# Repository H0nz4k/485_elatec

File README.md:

# 485_elatec

Hardware concept for an ELATEC TWN4 MultiTech 3 BLE carrier board with RS-485 / OSDP, wide-range DC input, door lock outputs, and a Raspberry Pi-side RS-485 gateway.

## Current contents

- `analyza_twn4_carrier.md` - design analysis and architecture notes
- `schema_twn4_carrier_rev_a.md` - first schematic-level design proposal
- `rpi_gateway_hw.md` - Raspberry Pi RS-485 gateway / HAT notes
- `kicad/twn4_access_system/` - KiCad concept schematic for the reader carrier and RPi gateway

The design is currently Rev A concept-level work. It still needs component selection, footprint assignment, detailed ERC review, PCB layout, and bench validation before hardware production.

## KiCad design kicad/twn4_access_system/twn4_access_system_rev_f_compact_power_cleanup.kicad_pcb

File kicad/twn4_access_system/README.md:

# KiCad: TWN4 access system

This is a concept KiCad project for two related hardware blocks:

- reader-side TWN4 carrier / door module
- Raspberry Pi-side RS-485 gateway / HAT

The project contains two schematic sheets:

- `twn4_access_system.kicad_sch` - Rev A concept drawing
- `twn4_access_system_rev_b.kicad_sch` - Rev B schematic draft with concrete symbols, named nets, candidate footprints, and both reader-side and Raspberry Pi-side hardware

The Rev B electrical design notes and preliminary BOM are documented in:

- `../../schema_electrical_rev_b.md`
- `../../bom_rev_b.csv`

Current Rev B KiCad status:

- netlist export works and contains the real schematic components/nets
- Rev B now includes explicit service-prototype passives, RS-485 termination/bias options, lock/relay/input support parts and testpoints
- ERC has no error-severity findings after the current pass
- remaining ERC messages are warnings from embedded one-off symbols and intentionally single-ended configuration nets
- no Rev B PCB has been validated yet

Next KiCad step: replace the embedded placeholder-style symbols with proper library symbols/aliases, lock exact manufacturer footprints, then create the first service PCB layout.

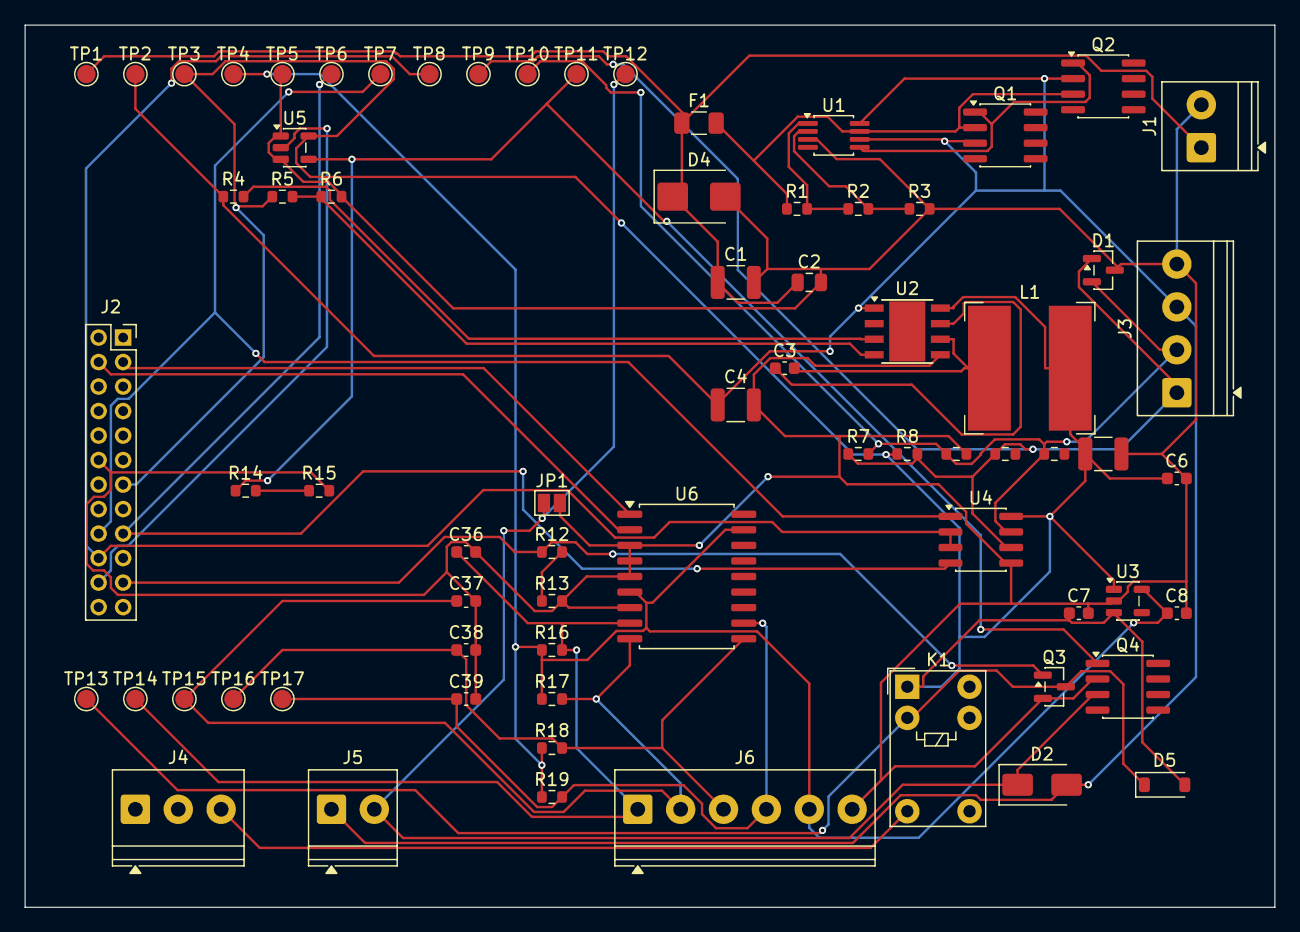
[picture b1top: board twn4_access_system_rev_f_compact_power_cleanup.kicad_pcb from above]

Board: 2 copper layers, 102.0 x 72.0 mm, 72 parts (0 on the bottom side), 32 nets.

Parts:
C1: 4.7uF 100V X7R input bulk; C_1210_3225Metric
C2: 100nF 100V input HF; C_0805_2012Metric
C3: 100nF BST; C_0603_1608Metric
C4: 22uF 100V buck input; C_1210_3225Metric
C5: 47uF 10V buck output; C_1210_3225Metric
C6: 100nF 5V HF; C_0603_1608Metric
C7: 1uF 3V3 LDO in; C_0603_1608Metric
C8: 1uF 3V3 LDO out; C_0603_1608Metric
C36: 10nF DOOR_IN filter; C_0603_1608Metric
C37: 10nF REX_IN filter; C_0603_1608Metric
C38: 10nF TAMPER_IN filter; C_0603_1608Metric
C39: 10nF AUX_IN filter; C_0603_1608Metric
D1: SM712 RS-485 TVS; SOT-23
D2: Lock flyback diode/TVS placeholder; D_SMA
D4: SMBJ58A input TVS; D_SMB
D5: Relay flyback diode; D_SOD-123
F1: 1.5A 60V+ fuse/PTC; Fuse_1206_3216Metric
J1: VIN 12-48V IN; TerminalBlock_Phoenix_PT-1,5-2-3.5-H_1x02_P3.50mm_Horizontal
J2: TWN4 MultiTech 3 BLE X2 socket; PinSocket_2x12_P2.00mm_Vertical
J3: RS-485 OUT A/B/+VIN/GND; TerminalBlock_Phoenix_PT-1,5-4-3.5-H_1x04_P3.50mm_Horizontal
J4: Relay contact COM/NC/NO; TerminalBlock_Phoenix_PT-1,5-3-3.5-H_1x03_P3.50mm_Horizontal
J5: LOCK OUT +VIN/SW-; TerminalBlock_Phoenix_PT-1,5-2-3.5-H_1x02_P3.50mm_Horizontal
J6: DOOR/REX/TAMPER/AUX inputs; TerminalBlock_Phoenix_PT-1,5-6-3.5-H_1x06_P3.50mm_Horizontal
JP1: LOCK SERVICE LINK; SolderJumper-2_P1.3mm_Open_Pad1.0x1.5mm
K1: Dry relay contact NO/NC/COM; Relay_SPDT_Omron_G5V-1
L1: 47uH shielded inductor; L_Bourns-SRN1060
Q1: Reverse/surge FET A 100V; SOIC-8_3.9x4.9mm_P1.27mm
Q2: Reverse/surge FET B 100V; SOIC-8_3.9x4.9mm_P1.27mm
Q3: Relay low-side driver; SOT-23
Q4: Lock low-side MOSFET 100V; SOIC-8_3.9x4.9mm_P1.27mm
R1: 1M UV/OV top placeholder; R_0603_1608Metric
R2: 100k UV/OV mid placeholder; R_0603_1608Metric
R3: 27k UV/OV bottom placeholder; R_0603_1608Metric
R4: 200k LM5164 RON; R_0603_1608Metric
R5: 604k 5V FB top; R_0603_1608Metric
R6: 100k 5V FB bottom; R_0603_1608Metric
R7: 120R RS485 TERM DNP/JMP; R_0603_1608Metric
R8: 680R RS485 bias pullup DNP/JMP; R_0603_1608Metric
R9: 680R RS485 bias pulldown DNP/JMP; R_0603_1608Metric
R10: 22R RS485 A series option; R_0603_1608Metric
R11: 22R RS485 B series option; R_0603_1608Metric
R12: 100R relay gate; R_0603_1608Metric
R13: 100k relay gate pulldown; R_0603_1608Metric
R14: 100R lock gate; R_0603_1608Metric
R15: 100k lock gate pulldown; R_0603_1608Metric
R16: 10k DOOR_IN pullup; R_0603_1608Metric
R17: 10k REX_IN pullup; R_0603_1608Metric
R18: 10k TAMPER_IN pullup; R_0603_1608Metric
R19: 10k AUX_IN pullup; R_0603_1608Metric
TP1: VIN_IN; TestPoint_Pad_D1.5mm
TP2: VIN_PROT; TestPoint_Pad_D1.5mm
TP3: +5V; TestPoint_Pad_D1.5mm
TP4: +3V3; TestPoint_Pad_D1.5mm
TP5: GND; TestPoint_Pad_D1.5mm
TP6: COM1_TX; TestPoint_Pad_D1.5mm
TP7: COM1_RX; TestPoint_Pad_D1.5mm
TP8: GPIO4_RS485_DIR; TestPoint_Pad_D1.5mm
TP9: RS485_A; TestPoint_Pad_D1.5mm
TP10: RS485_B; TestPoint_Pad_D1.5mm
TP11: LOCK_GATE_5V; TestPoint_Pad_D1.5mm
TP12: LOCK_SW_LOW; TestPoint_Pad_D1.5mm
TP13: RELAY_COIL_LOW; TestPoint_Pad_D1.5mm
TP14: DOOR_IN; TestPoint_Pad_D1.5mm
TP15: REX_IN; TestPoint_Pad_D1.5mm
TP16: TAMPER_IN; TestPoint_Pad_D1.5mm
TP17: AUX_IN; TestPoint_Pad_D1.5mm
U1: LTC4367 surge/OV/UV protector; MSOP-8_3x3mm_P0.65mm
U2: LM5164 12-48V to 5V buck; Texas_HSOP-8-1EP_3.9x4.9mm_P1.27mm
U3: TLV75533 3.3V local rail; SOT-23-5
U4: THVD1450 reader RS-485 transceiver; SOIC-8_3.9x4.9mm_P1.27mm
U5: 5V gate buffer for lock FET; SOT-23-5
U6: MCP23008 door input expander; SOIC-18W_7.5x11.6mm_P1.27mm

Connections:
+3V3: C8.1, J6.5, R16.1, R17.1, R18.1, R19.1, TP4.1, U3.5, U6.6, U6.17
+5V: C5.1, C6.1, C7.1, D5.2, J2.13, K1.1, L1.2, R5.1, R8.1, TP3.1, U2.8, U3.1, U3.3, U4.8, U5.5
AUX_IN: C39.1, J6.4, R19.2, TP17.1, U6.11
BST_NODE: C3.1, U2.7
COM1_RX: J2.18, TP7.1, U4.1
COM1_TX: J2.17, TP6.1, U4.4
DOOR_IN: C36.1, J6.1, R16.2, TP14.1, U6.8
FB_5V: R5.2, R6.1, U2.4
GND: C1.2, C2.2, C4.2, C5.2, C6.2, C7.2, C8.2, C36.2, C37.2, C38.2, C39.2, D1.3, D4.2, J1.2, J2.12, J3.4, J6.6, JP1.2, Q3.2, Q4.2, R3.2, R6.2, R9.2, R13.2, R15.2, TP5.1, U1.3, U2.5, U3.2, U4.5, U5.1, U5.3, U6.3, U6.4, U6.5, U6.7
GPIO4_RS485_DIR: J2.20, TP8.1, U4.2, U4.3
GPIO5_RELAY: J2.21, Q3.1, R12.1
GPIO6_LOCK: J2.22, U5.2
I2C_SCL: J2.3, U6.1
I2C_SDA: J2.4, U6.2
LOCK_GATE_5V: Q4.1, R14.1, TP11.1, U5.4
LOCK_GATE_DRV: R14.2, R15.1
LOCK_SW_LOW: D2.1, J5.2, JP1.1, Q4.3, TP12.1
OV_NODE: R2.2, R3.1, U1.2
PROT_GATE: Q1.1, Q2.1, U1.5
RELAY_COIL_LOW: D5.1, K1.2, Q3.3, TP13.1
RELAY_GATE: R12.2, R13.1
RELAY_NO: J4.3, K1.5
REX_IN: C37.1, J6.2, R17.2, TP15.1, U6.9
RON_NODE: R4.2, U2.3
RS485_A: D1.1, J3.1, R7.1, R8.2, R10.1, TP9.1, U4.6
RS485_B: D1.2, J3.2, R7.2, R9.1, R11.1, TP10.1, U4.7
SW_NODE: C3.2, L1.1, U2.6
TAMPER_IN: C38.1, J6.3, R18.2, TP16.1, U6.10
UV_NODE: R1.2, R2.1, U1.1
VIN_FUSED: F1.2, Q1.2, Q2.3, R1.1, U1.7
VIN_IN: C1.1, C2.1, D4.1, F1.1, J1.1, TP1.1
VIN_PROT: C4.1, D2.2, J3.3, J5.1, Q1.3, Q2.2, R4.1, TP2.1, U1.6, U1.8, U2.1

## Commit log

2026-05-06 Initial TWN4 carrier and RS-485 gateway concept
2026-05-12 rev-e: add compact carrier prototype package
2026-05-12 rev-f: add power layout audit checkpoint
